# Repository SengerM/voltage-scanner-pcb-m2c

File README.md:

# voltage-scanner-pcb-m2c

[KiCad](http://kicad-pcb.org/) project for the M2C board. This board implements two independent channels, to connect up to two zeners. The schematic of this board can be found in [this link](export/Scanner-zeners.pdf). Below is the layout.

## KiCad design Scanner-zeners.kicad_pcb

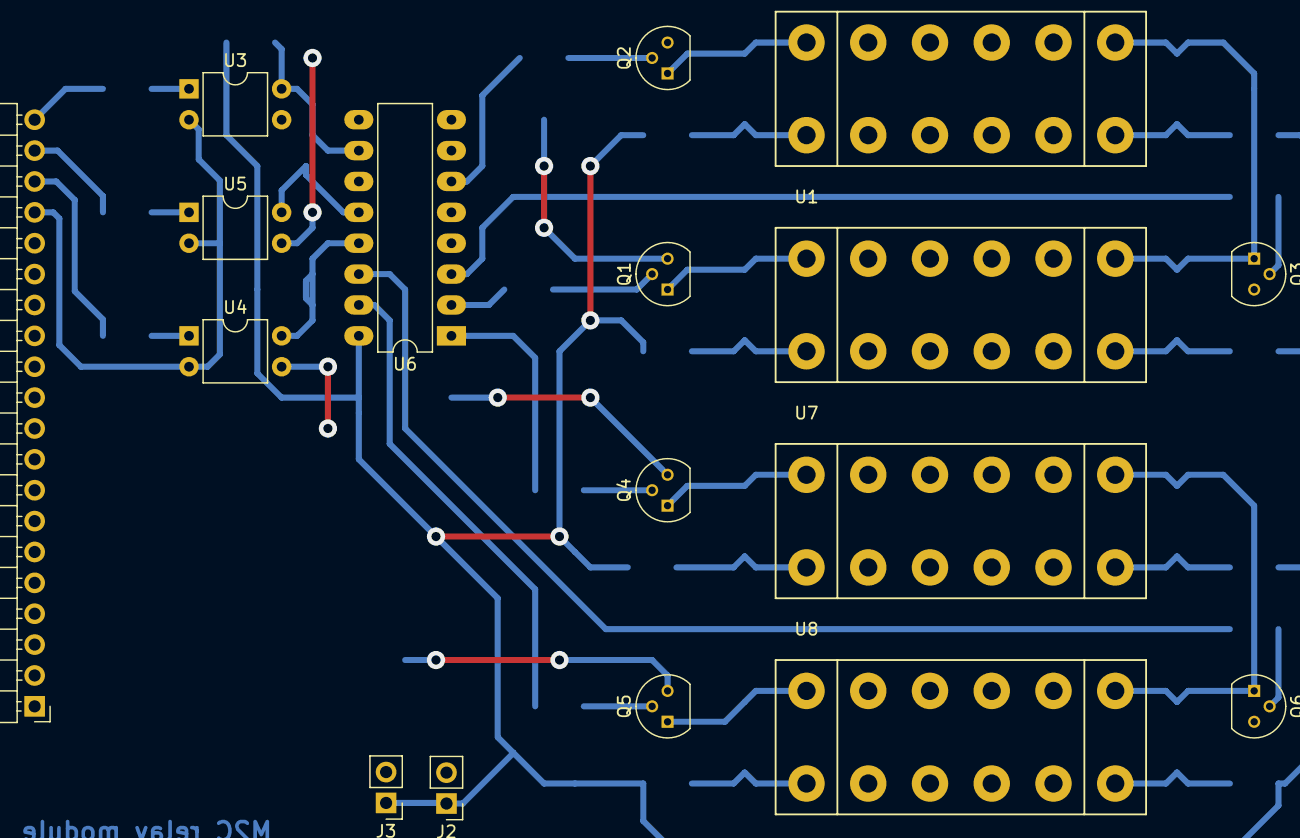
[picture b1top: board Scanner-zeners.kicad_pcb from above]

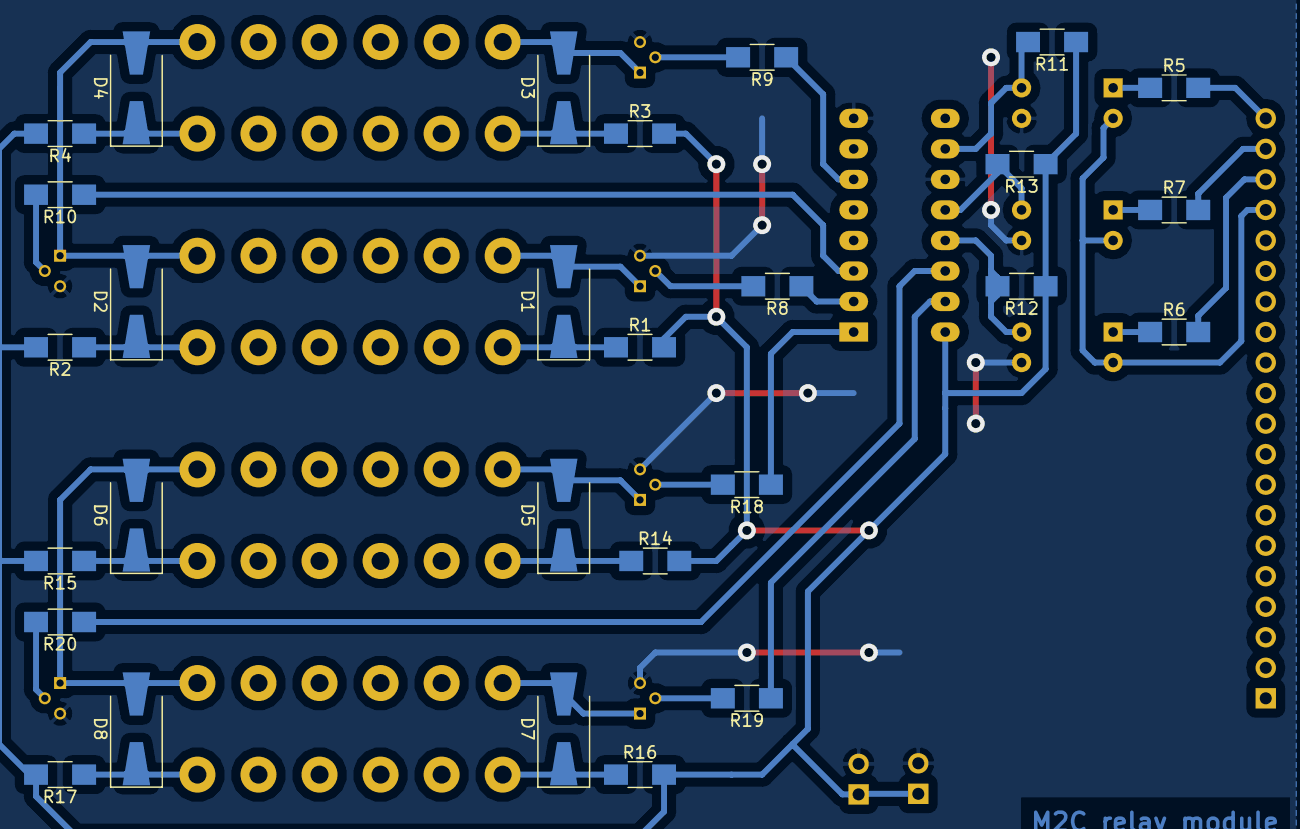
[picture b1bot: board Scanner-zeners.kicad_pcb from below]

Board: 2 copper layers, 45 parts (28 on the bottom side), 38 nets.

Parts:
D1, D2, D3, D4, D5, D6, D7, D8: 1N4007; D_SMA-SMB_Universal_Handsoldering
J1: Conn_01x20_Male; PinHeader_1x20_P2.54mm_Horizontal
J2, J3: Battery connector; PinHeader_1x02_P2.54mm_Vertical
Q1, Q2, Q3, Q4, Q5, Q6: BC548; TO-92_Molded_Narrow
R1, R2, R3, R4, R5, R6, R7, R14, R15, R16, R17: 220; R_1206_HandSoldering
R8, R9, R10, R11, R12, R13, R18, R19, R20: 2k2; R_1206_HandSoldering
U1, U2, U7, U8: S4EBL25V
U3, U4, U5: PC817; DIP-4_W7.62mm
U6: 4028; DIP-16_W7.62mm_LongPads

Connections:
+12V: J2.1, J3.1, R1.2, R2.2, R3.2, R4.2, R11.1, R12.1, R13.1, R14.2, R15.2, R16.2, R17.2, U6.16
/Arduino_GND: J1.17, U3.2, U4.2, U5.2
/pin0: J1.20, R5.2
/pin1: J1.18, R6.2
/pin2: J1.19, R7.2
CH0_A: R8.1, U6.2
CH0_B: R9.1, U6.6
CH0_OPEN: R10.1, U6.3
CH1_A: R18.1, U6.1
CH1_B: R19.1, U6.15
CH1_OPEN: R20.1, U6.14
GNDA: J2.2, J3.2, Q1.3, Q2.3, Q3.3, Q4.3, Q5.3, Q6.3, U3.3, U4.3, U5.3, U6.8, U6.11
unnamed: D1.1, R1.1, U1.1
unnamed: D1.2, Q1.1, U1.12
unnamed: D2.1, R2.1, U1.6
unnamed: D2.2, D4.2, Q3.1, U1.7, U2.7
unnamed: D3.1, R3.1, U2.1
unnamed: D3.2, Q2.1, U2.12
unnamed: D4.1, R4.1, U2.6
unnamed: D5.1, R14.1, U7.1
unnamed: D5.2, Q4.1, U7.12
unnamed: D6.1, R15.1, U7.6
unnamed: D6.2, D8.2, Q6.1, U7.7, U8.7
unnamed: D7.1, R16.1, U8.1
unnamed: D7.2, Q5.1, U8.12
unnamed: D8.1, R17.1, U8.6
unnamed: Q1.2, R8.2
unnamed: Q2.2, R9.2
unnamed: Q3.2, R10.2
unnamed: Q4.2, R18.2
unnamed: Q5.2, R19.2
unnamed: Q6.2, R20.2
unnamed: R5.1, U3.1
unnamed: R6.1, U4.1
unnamed: R7.1, U5.1
unnamed: R11.2, U3.4, U6.10
unnamed: R12.2, U4.4, U6.13
unnamed: R13.2, U5.4, U6.12

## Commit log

2019-05-22 Primer commit
2019-05-22 Modifiqué el esquemático para tener más pines.
2019-05-22 Version para back panel lista
2019-05-23 Added readme
2019-05-23 Some changes
